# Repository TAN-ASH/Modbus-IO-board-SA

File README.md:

# Modbus-IO-board-SA
Modbus IO board SA new changes made in the board for 80x82x86 dimension encloser

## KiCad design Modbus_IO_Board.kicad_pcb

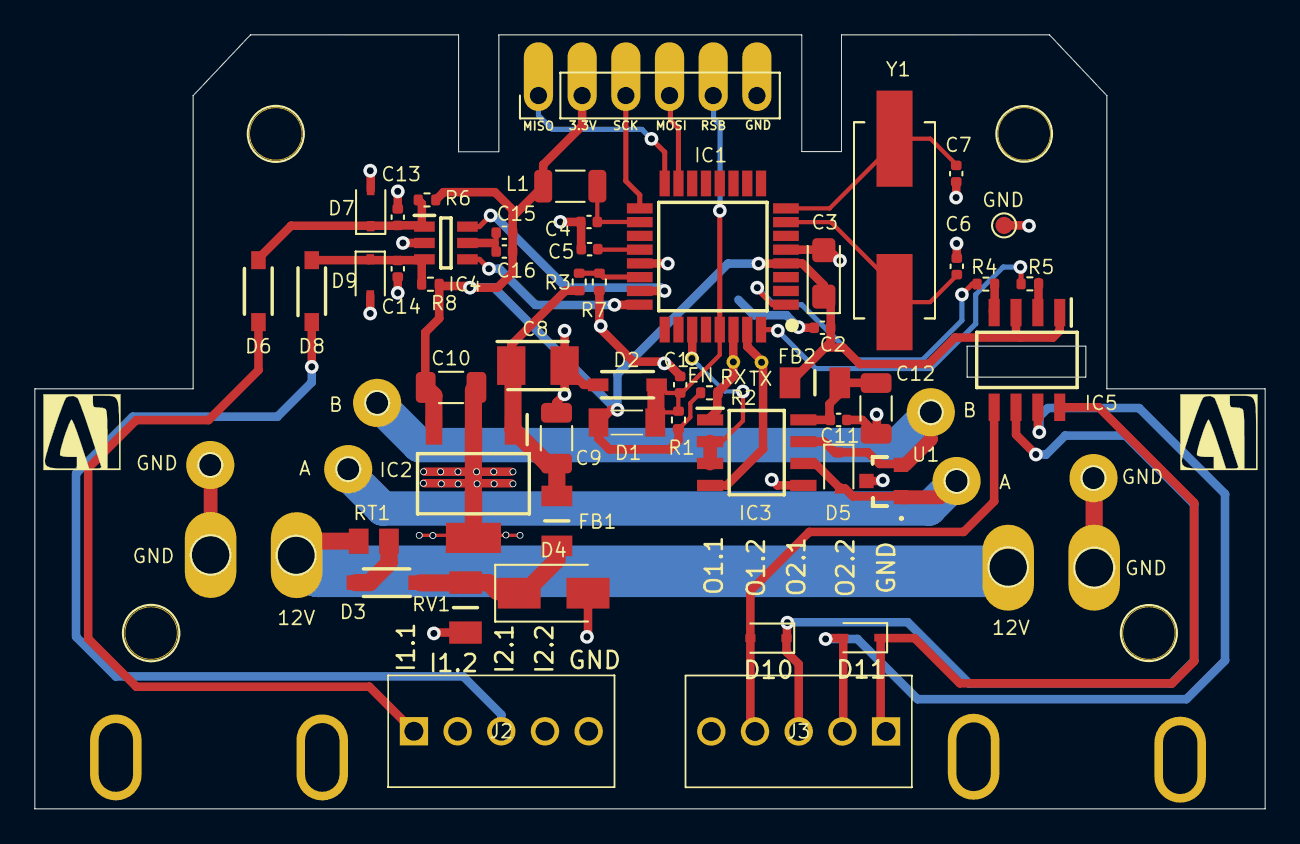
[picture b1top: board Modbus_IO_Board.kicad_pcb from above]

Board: 2 copper layers, 71.5 x 45.0 mm, 72 parts (0 on the bottom side), 36 nets.

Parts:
12V, 12V#2: TestPoint; TestPoint_Pad_D1.0mm
A: TestPoint; TestPoint_Pad_D1.0mm
A#2: TestPoint; TestPoint_Pad_D1.0mm
B: TestPoint; TestPoint_Pad_D1.0mm
B#2: TestPoint; TestPoint_Pad_D1.0mm
C1, C16: 1uF; C_0402_1005Metric
C2: 10nF; C_0402_1005Metric
C3: 1uF; CP_EIA-3216-18_Kemet-A
C4, C5, C11, C13, C14: 100nF; C_0402_1005Metric
C6, C7: 22pF; C_0402_1005Metric
C8: 10uF35V; CAPPM3528X210N
C9: 0.1uF35V; C_1206_3216Metric
C10, C12: 4.7uF; C_1206_3216Metric
C15: 0.1uF; C_0402_1005Metric
D1: D; FDLL4448
D2: D_Zener; SOD3716X145N
D3, D6, D8: B5819W-TP; SOD3716X135N
D4: D_TVS; D_SMA
D5, D7, D9, D10, D11: D_TVS; D_SOD-323
EN: TestPoint; TestPoint_Pad_D1.0mm
FB1, FB2: 74279218; BEADC3216X130N
GND: TestPoint; TestPoint_Pad_D1.0mm
GND#2, GND#3, GND#4, GND#5: TestPoint; TestPoint_Pad_D1.0mm
H1, H2, H3, H4: MountingHole; TestPoint_Plated_Hole_D3.0mm
IC1: ATMEGA328PB-AN; QFP80P900X900X120-32N
IC2: TPS7B6933QDCYRQ1; SOT230P700X180-4N
IC3: MAX3072EASA+; SOIC127P600X175-8N
IC4: SN74LVC2G14DBVRG4; SOT95P280X145-6N
IC5: LTV-206; SOIC127P610X363-8N
J1: Conn_01x06_Male; PinSocket_1x06_P2.54mm_Vertical
J2: 2.54mm pitch Terminal Block; 2828345
J3: 282834-5; 2828345
L1: 10uH; L_1206_3216Metric
R1, R2, R6, R7, R8: 4K7; R_0402_1005Metric
R3: 100K; R_0402_1005Metric
R4, R5: 330; R_0402_1005Metric
RT1: PRG21BC4R7MM1RA; THRMC2012X110N
RV1: Varistor; VARC3216X145N
RX: TestPoint; TestPoint_Pad_D1.0mm
TP2: TestPoint; TestPoint_Pad_D1.0mm
U1: PSM712-LF-T7; PSM712LFT7
Y1: 7.37MHz; ABLS373728MHZD4YT
Z1, Z1#2, Z2, Z2#2: CONN_01X01; 1pin

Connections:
+3V3: C2.1, C3.1, C10.1, C15.1, C16.1, D1.1, FB2.2, IC1.4, IC2.3, IC5.1, IC5.3, J1.2, L1.1, R1.1, R2.1, R6.1, R8.1
+12V: 12V.1, 12V#2.1, RT1.1
/1Y: IC1.23, IC4.6
/2Y: IC1.24, IC4.4
/Data_A: A.1, A#2.1, D5.2, IC3.6, U1.1
/Data_B: B.1, B#2.1, D5.1, IC3.7, U1.2
/I1-1: D6.1, J2.1
/I2-1: D8.1, J2.3
/MAX_EN: EN.1, IC1.27, IC3.2, IC3.3
/MISO: IC1.16, J1.1
/MOSI: IC1.15, J1.4
/OUT1: IC1.32, R5.1
/OUT2: IC1.1, R4.1
/RSB: C1.1, D1.2, D2.1, IC1.29, J1.5, R1.2
/RXD: IC1.30, IC3.1, R2.2, RX.1
/SCK: IC1.17, J1.3
/TXD: IC1.31, IC3.4, TP2.1
/Vin: IC1.22, R3.2, R7.1
GND: C1.2, C2.2, C3.2, C4.1, C5.2, C6.2, C7.2, C8.2, C9.2, C10.2, C11.2, C12.2, C13.2, C14.2, D2.2, D4.2, D7.2, D9.2, GND.1, GND#2.1, GND#3.1, GND#4.1, GND#5.1, IC1.5, IC1.21, IC2.2, IC2.4, IC3.5, IC4.2, J1.6, J2.2, J2.4, J2.5, J3.5, R7.2, RV1.2, U1.3
unnamed: C4.2, IC1.20
unnamed: C5.1, IC1.18, L1.2
unnamed: C6.1, IC1.7, Y1.1
unnamed: C7.1, IC1.8, Y1.2
unnamed: C8.1, C9.1, FB1.2, IC2.1, R3.1
unnamed: C11.1, C12.1, FB2.1, IC3.8
unnamed: C13.1, D6.2, D7.1, IC4.1, R6.2
unnamed: C14.1, D8.2, D9.1, IC4.3, R8.2
unnamed: C15.2, C16.2, IC4.5
unnamed: D3.1, D4.1, FB1.1, RV1.1
unnamed: D3.2, RT1.2
unnamed: D10.1, IC5.6, J3.3
unnamed: D10.2, IC5.5, J3.4
unnamed: D11.1, IC5.8, J3.1
unnamed: D11.2, IC5.7, J3.2
unnamed: IC5.2, R5.2
unnamed: IC5.4, R4.2

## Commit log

2021-10-30 Unfinished PCB IO board
2021-11-01 PCB awaiting Review
2021-11-03 Review Pending
2021-11-08 Review and Approval Pending
